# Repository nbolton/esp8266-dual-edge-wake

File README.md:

# ESP8266 dual edge wake

This module will wake an ESP8266 from deep sleep when a sensor value changes (e.g. push button, float sensor, or other reed sensor). 

**Disclaimer:** If you need to do this, then you should probably use a different MCU that supports deep sleep interrupt on edge. But, if like me, you bought many ESP8266s and want to use them in a project where you have this requirement...

Connect input to the sensor, and output to the RST pin on the ESP8266.

*Note: Above is Rev 1 (latest is Rev 1a)*

When the input changes (goes from high to low or low to high), a short pulse is generated on the output which wakes the ESP8266 from deep sleep.

Note: The blue line above is mis-labeled as Q1, and should read Q3.

Either circuit A or B can be used. A is a dual edge monostable trigger, and B is an edge to glitch conveter (XOR with delay). 
Solder the circuit jumper to choose between circuit A or B (the center pad is the input). 

For circuit A, solder either the leading or falling jumper (or both can be soldered to pulse on both edges).
For circuit B, a pulse will always be generated on both edges.

VCC min 2.5 V, max 6.0 V.

Example use case: Wake your ESP8266 and report a float sensor value change (e.g. when a water tank is full).

*Note: Resistor bodge was needed for board Rev 1 (now obsolete, replaced by Rev 1b which fixed the issue).*

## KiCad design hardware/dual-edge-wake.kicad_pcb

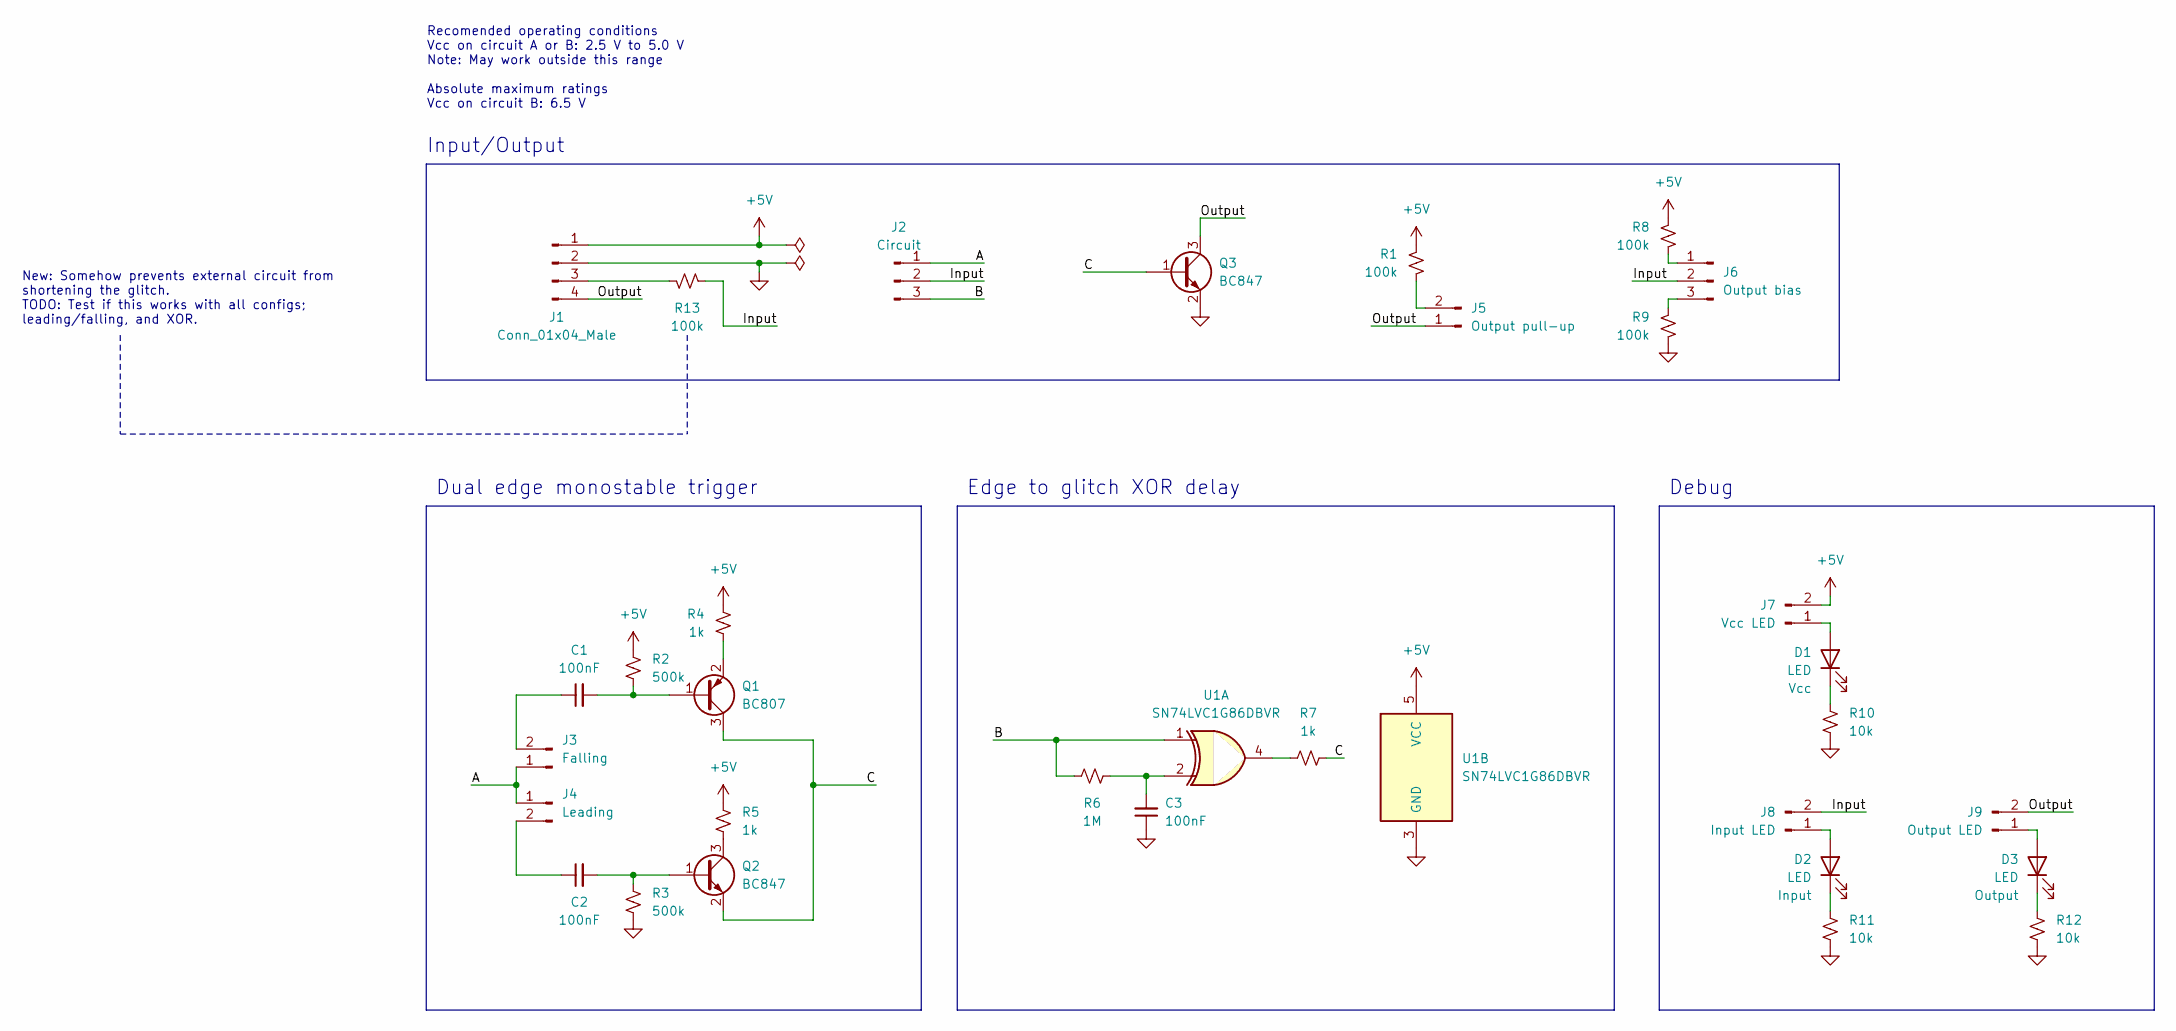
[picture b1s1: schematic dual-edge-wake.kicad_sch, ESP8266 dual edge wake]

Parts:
C1, C2, C3: 100nF; C_0805_2012Metric_Pad1.18x1.45mm_HandSolder; LCSC C1711
D1, D2, D3: LED; LED_0603_1608Metric_Pad1.05x0.95mm_HandSolder; LCSC C118339
J1: Conn_01x04_Male; PinHeader_1x04_P2.54mm_Vertical
J2: Circuit; SolderJumper-3_P1.3mm_Open_RoundedPad1.0x1.5mm
J3: Falling; SolderJumper-2_P1.3mm_Open_RoundedPad1.0x1.5mm
J4: Leading; SolderJumper-2_P1.3mm_Open_RoundedPad1.0x1.5mm
J5: Output pull-up; SolderJumper-2_P1.3mm_Open_RoundedPad1.0x1.5mm
J6: Output bias; SolderJumper-3_HL
J7: Vcc LED; SolderJumper-2_P1.3mm_Open_RoundedPad1.0x1.5mm
J8: Input LED; SolderJumper-2_P1.3mm_Open_RoundedPad1.0x1.5mm
J9: Output LED; SolderJumper-2_P1.3mm_Open_RoundedPad1.0x1.5mm
Q1: BC807; SOT-23_Handsoldering; LCSC C88012
Q2, Q3: BC847; SOT-23_Handsoldering; LCSC C57668
R1, R8, R9, R13: 100k; R_0805_2012Metric_Pad1.20x1.40mm_HandSolder; LCSC C2077866
R2, R3: 500k; R_0805_2012Metric_Pad1.20x1.40mm_HandSolder; LCSC C2077866
R4, R5, R7: 1k; R_0805_2012Metric_Pad1.20x1.40mm_HandSolder; LCSC C79496
R6: 1M; R_0805_2012Metric_Pad1.20x1.40mm_HandSolder; LCSC C413339
R10, R11, R12: 10k; R_0805_2012Metric_Pad1.20x1.40mm_HandSolder; LCSC C2077866
U1: SN74LVC1G86DBVR; SOT-23-5_HandSoldering; LCSC C402161

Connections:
+5V: J1.1, J7.2, R1.2, R2.1, R4.1, R5.1, R8.2, U1.5 (VCC)
/A: J2.1, J3.1, J4.1
/B: J2.3, R6.2, U1.1
/C: Q1.3 (C), Q2.2 (E), Q3.1 (B), R7.2
/Input: J2.2, J6.2, J8.2, R13.1
/Output: J1.4, J5.1, J9.2, Q3.3 (C)
GND: C3.1, J1.2, Q3.2 (E), R3.1, R9.1, R10.1, R11.1, R12.1, U1.3 (GND)
unnamed: C3.2, R6.1, U1.2
unnamed: D1.2 (A), J7.1
unnamed: D1.1 (K), R10.2
unnamed: D2.2 (A), J8.1
unnamed: D2.1 (K), R11.2
unnamed: D3.2 (A), J9.1
unnamed: D3.1 (K), R12.2
unnamed: J1.3, R13.2
unnamed: C1.1, J3.2
unnamed: C2.1, J4.2
unnamed: J5.2, R1.1
unnamed: J6.1, R8.1
unnamed: J6.3, R9.2
unnamed: C1.2, Q1.1 (B), R2.2
unnamed: Q1.2 (E), R4.2
unnamed: C2.2, Q2.1 (B), R3.2
unnamed: Q2.3 (C), R5.2
unnamed: R7.1, U1.4

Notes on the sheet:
Edge to glitch XOR delay
Dual edge monostable trigger
Debug
New: Somehow prevents external circuit from shortening the glitch. TODO: Test if this works with all configs; leading/falling, and XOR.
Recomended operating conditions Vcc on circuit A or B: 2.5 V to 5.0 V Note: May work outside this range Absolute maximum ratings Vcc on circuit B: 6.5 V
Input/Output

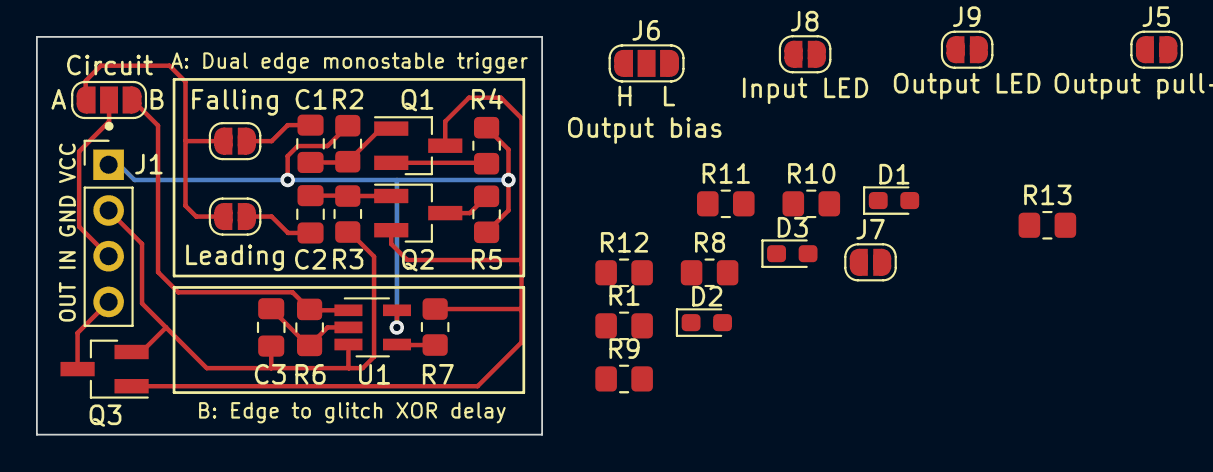
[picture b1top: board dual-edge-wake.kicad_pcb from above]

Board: 2 copper layers, 28.1 x 22.1 mm, 32 parts (0 on the bottom side), 25 nets.

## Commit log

2023-01-28 WIP (need to fix alignment)
2023-01-28 Add custom RC jumper
2023-01-28 Assign value to XOR
2023-01-28 Assigned footprints and started PCB
2023-01-29 Finished first PCB
2023-01-29 Rename project dir
2023-02-06 Fixed #2
    Add resistor between circuit outputs, removed pull-up on circuit A input. Also add rear SS
2023-02-07 Tidied up SS, updated rev
2023-02-24 WIP - Add pull ups and LEDs
2023-03-05 Add todo to PCB
2023-05-18 Add input resistor
